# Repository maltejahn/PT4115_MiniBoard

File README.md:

Aim:
- small board with a PT4115 LED constant current source -> up to 1.2 A
- dimmable with a 5V PWM signal (PWM frequency up to 50 kHz acc. to datasheet)
- single sided so it can be mounted to a heat sink (using 2 M4 Bolts)
- connected using pin header (0.1") of soldered directly
- shouldnt smoke immediately

ToDo:
- some measurements...

Tasks:
- finalize schematic  - done
- finalize pcb - done
- Gerbers, order pcb - tbd
- BOM, assemble instructions - tbd
- assemble - tbd
- test - tbd
- report - tbd

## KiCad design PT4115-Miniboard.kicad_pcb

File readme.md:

Aim:
- small board with a PT4115 LED constant current source -> up to 1.2 A
- dimmable with a 5V PWM signal (PWM frequency up to 50 kHz acc. to datasheet)
- single sided so it can be mounted to a heat sink (using 2 M4 Bolts)
- connected using pin header (0.1") of soldered directly

ToDo:
- some measurements...

Tasks:
finalize schematic  - done
finalize pcb - done
Gerbers, order pcb - tbd
BOM, assemble instructions - tbd
assemble - tbd
test - tbd
report - tbd

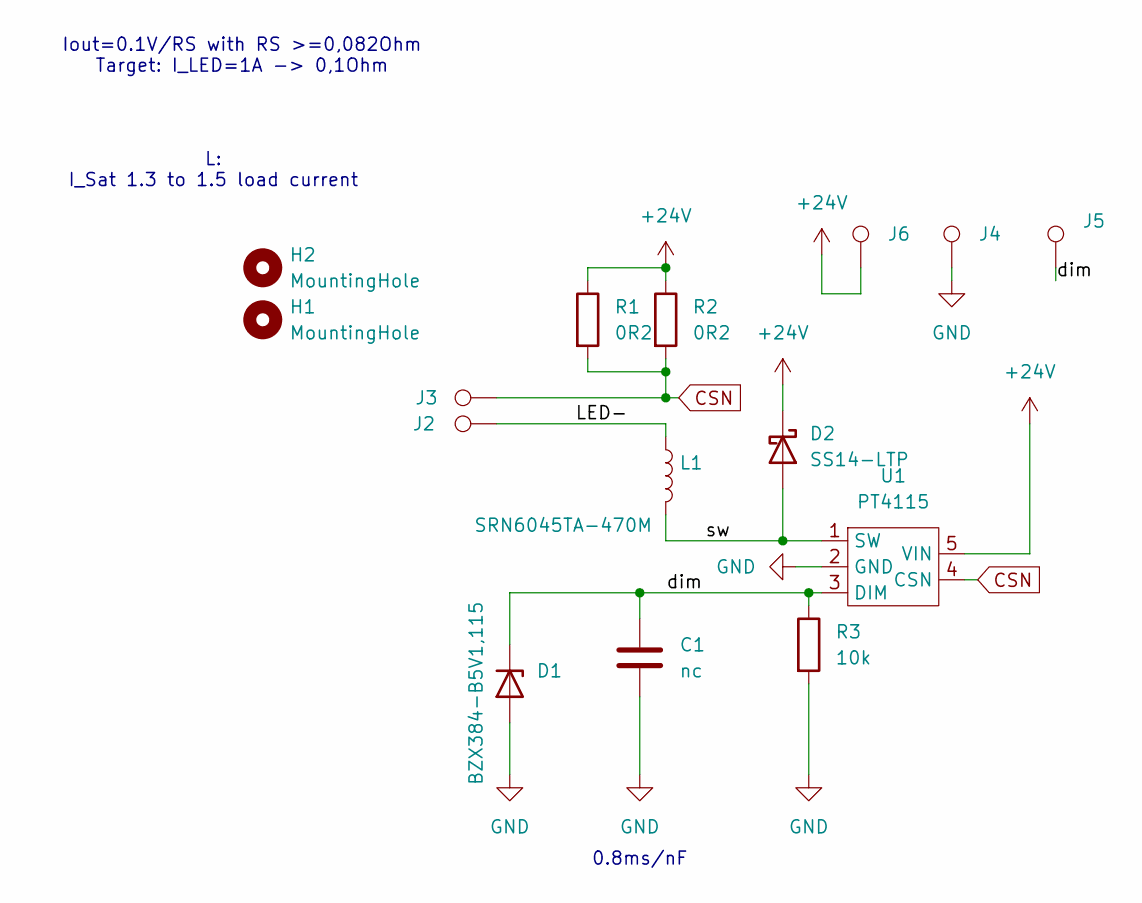
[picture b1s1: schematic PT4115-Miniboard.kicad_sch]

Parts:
C1: nc; C_0805_2012Metric
D1: BZX384-B5V1,115; D_SC-80_HandSoldering; Mouser 771-BZX384-B5V1-T/R
D2: SS14-LTP; D_SMA_Handsoldering; Mouser 833-SS14-LTP
H1, H2: MountingHole; MountingHole_3.2mm_M3_ISO14580
J2, J3, J4, J5, J6: TestPoint; Solder_Pad_5x1.3mm
L1: SRN6045TA-470M; L_Bourns_SRN6045TA; Mouser SRN6045TA-470M
R1, R2: 0R2; R_1210_3225Metric; Mouser RCWE1210R200FKEA
R3: 10k; R_0805_2012Metric; Mouser RC0805FR-0710KL
U1: PT4115; SOT-89-5_Handsoldering

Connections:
+24V: D2.1 (K), J6.1, R1.1, R2.1, U1.5 (VIN)
/LED-: J2.1, L1.1
/dim: C1.1, D1.1 (K), J5.1, R3.1, U1.3 (DIM)
/sw: D2.2 (A), L1.2, U1.1 (SW)
CSN: J3.1, R1.2, R2.2, U1.4 (CSN)
GND: C1.2, D1.2 (A), J4.1, R3.2, U1.2 (GND)

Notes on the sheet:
Iout=0.1V/RS with RS >=0,082Ohm Target: I_LED=1A -> 0,1Ohm
L: I_Sat 1.3 to 1.5 load current
0.8ms/nF

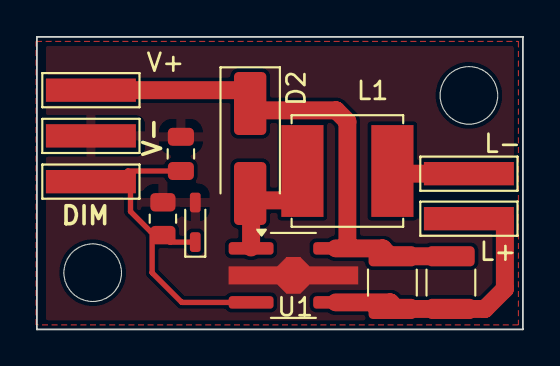
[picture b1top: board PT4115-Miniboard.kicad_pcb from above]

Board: 2 copper layers, 27.0 x 16.2 mm, 15 parts (0 on the bottom side), 6 nets.

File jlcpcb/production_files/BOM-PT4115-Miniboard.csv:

Comment,Designator,Footprint,LCSC
TestPoint,J5,Solder_Pad_5x1.3mm,
PT4115,U1,SOT-89-5_Handsoldering,
TestPoint,J6,Solder_Pad_5x1.3mm,
TestPoint,J4,Solder_Pad_5x1.3mm,
MountingHole,H2,MountingHole_3.2mm_M3_ISO14580,
0R2,R2,R_1210_3225Metric,
TestPoint,J2,Solder_Pad_5x1.3mm,
SRN6045TA-470M,L1,L_Bourns_SRN6045TA,
" BZX384-B5V1,115",D1,D_SC-80_HandSoldering,
0R2,R1,R_1210_3225Metric,
MountingHole,H3,MountingHole_4.3mm_M4,
TestPoint,J3,Solder_Pad_5x1.3mm,
SS14-LTP,D2,D_SMA_Handsoldering,
nc,C1,C_0805_2012Metric,
MountingHole,H1,MountingHole_3.2mm_M3_ISO14580,
10k,R3,R_0805_2012Metric,

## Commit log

2024-06-21 removed file
2024-06-21 readme updated
2024-06-21 image added
2024-06-21 image
2024-06-21 clarified readme
2024-06-21 added image of pcb - again
